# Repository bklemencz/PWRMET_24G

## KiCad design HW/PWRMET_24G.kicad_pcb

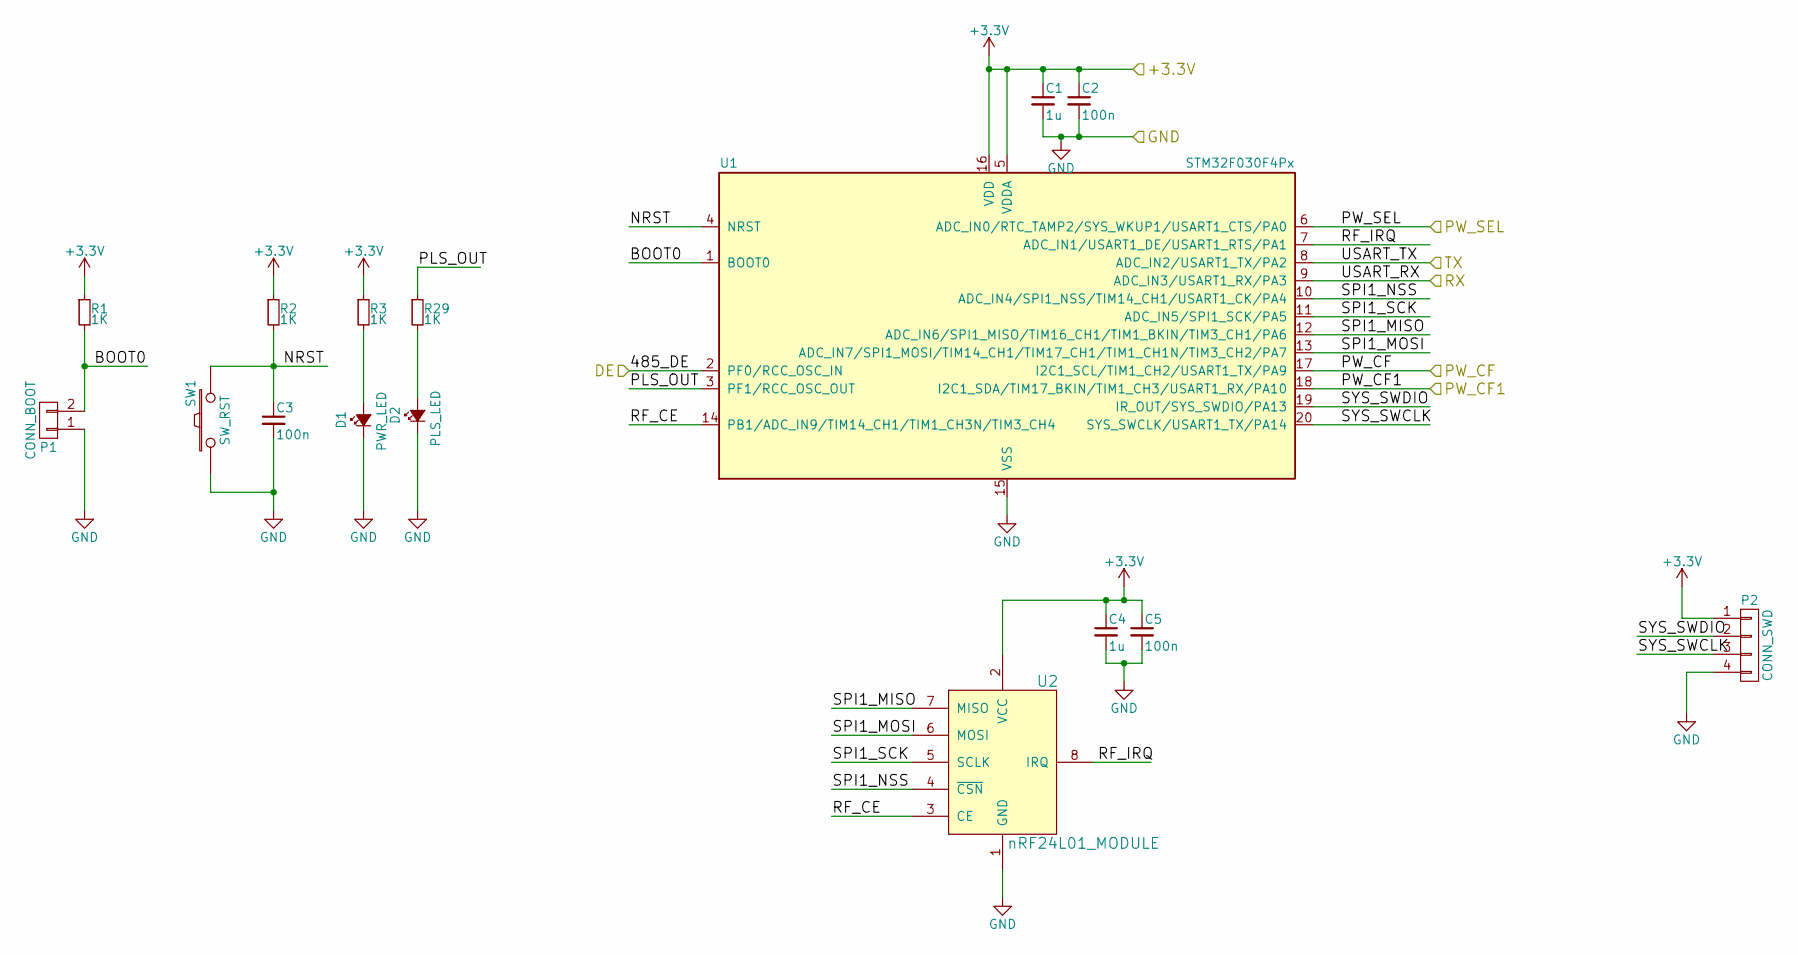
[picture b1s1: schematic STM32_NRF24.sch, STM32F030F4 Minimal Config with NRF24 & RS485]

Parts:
C1, C4: 1u; C_0805
C2, C3, C5: 100n; C_0805
D1: PWR_LED; LED_0805
D2: PLS_LED; LED_D5.0mm
P1: CONN_BOOT; Pin_Header_Straight_1x02_Pitch2.54mm
P2: CONN_SWD; Pin_Header_Straight_1x04_Pitch2.54mm
R1, R2, R3, R29: 1K; R_0805
SW1: SW_RST; SW_SPST_TACT_SMD_3X6
U1: STM32F030F4Px; TSSOP-20_4.4x6.5mm_Pitch0.65mm
U2: nRF24L01_MODULE; NRF24L01_MODULE

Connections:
+3V3: C1.1, C2.1, C4.1, C5.1, P2.1, R1.1, R2.1, R3.1, U1.5 (VDDA), U1.16 (VDD), U2.2 (VCC); also elsewhere on the board
/HLW8012/CF: U1.17 (I2C1_SCL/TIM1_CH2/USART1_TX/PA9); also elsewhere on the board
/HLW8012/CF1: U1.18 (I2C1_SDA/TIM17_BKIN/TIM1_CH3/USART1_RX/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); also elsewhere on the board
/RS485_ISOL/DE: U1.2 (PF0/RCC_OSC_IN); also elsewhere on the board
/RS485_ISOL/RX: U1.9 (ADC_IN3/USART1_RX/PA3); also elsewhere on the board
/RS485_ISOL/TX: U1.8 (ADC_IN2/USART1_TX/PA2); also elsewhere on the board
/STM32_NRF24/BOOT0: P1.2, R1.2, U1.1 (BOOT0)
/STM32_NRF24/NRST: C3.1, R2.2, SW1.2, U1.4 (NRST)
/STM32_NRF24/PLS_OUT: R29.1, U1.3 (PF1/RCC_OSC_OUT)
/STM32_NRF24/PW_SEL: U1.6 (ADC_IN0/RTC_TAMP2/SYS_WKUP1/USART1_CTS/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); also elsewhere on the board
/STM32_NRF24/RF_CE: U1.14 (PB1/ADC_IN9/TIM14_CH1/TIM1_CH3N/TIM3_CH4), U2.3 (CE)
/STM32_NRF24/RF_IRQ: U1.7 (ADC_IN1/USART1_DE/USART1_RTS/PA1), U2.8 (IRQ)
/STM32_NRF24/SPI1_MISO: U1.12 (ADC_IN6/SPI1_MISO/TIM16_CH1/TIM1_BKIN/T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), U2.7 (MISO)
/STM32_NRF24/SPI1_MOSI: U1.13 (ADC_IN7/SPI1_MOSI/TIM14_CH1/TIM17_CH1/T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), U2.6 (MOSI)
/STM32_NRF24/SPI1_NSS: U1.10 (ADC_IN4/SPI1_NSS/TIM14_CH1/USART1_CK/PA4), U2.4 (~CSN)
/STM32_NRF24/SPI1_SCK: U1.11 (ADC_IN5/SPI1_SCK/PA5), U2.5 (SCLK)
/STM32_NRF24/SYS_SWCLK: P2.3, U1.20 (SYS_SWCLK/USART1_TX/PA14)
/STM32_NRF24/SYS_SWDIO: P2.2, U1.19 (IR_OUT/SYS_SWDIO/PA13)
GND: C1.2, C2.2, C3.2, C4.2, C5.2, D1.1 (K), D2.1 (K), P1.1, P2.4, SW1.1, U1.15 (VSS), U2.1 (GND); also elsewhere on the board
unnamed: D1.2 (A), R3.2
unnamed: D2.2 (A), R29.2

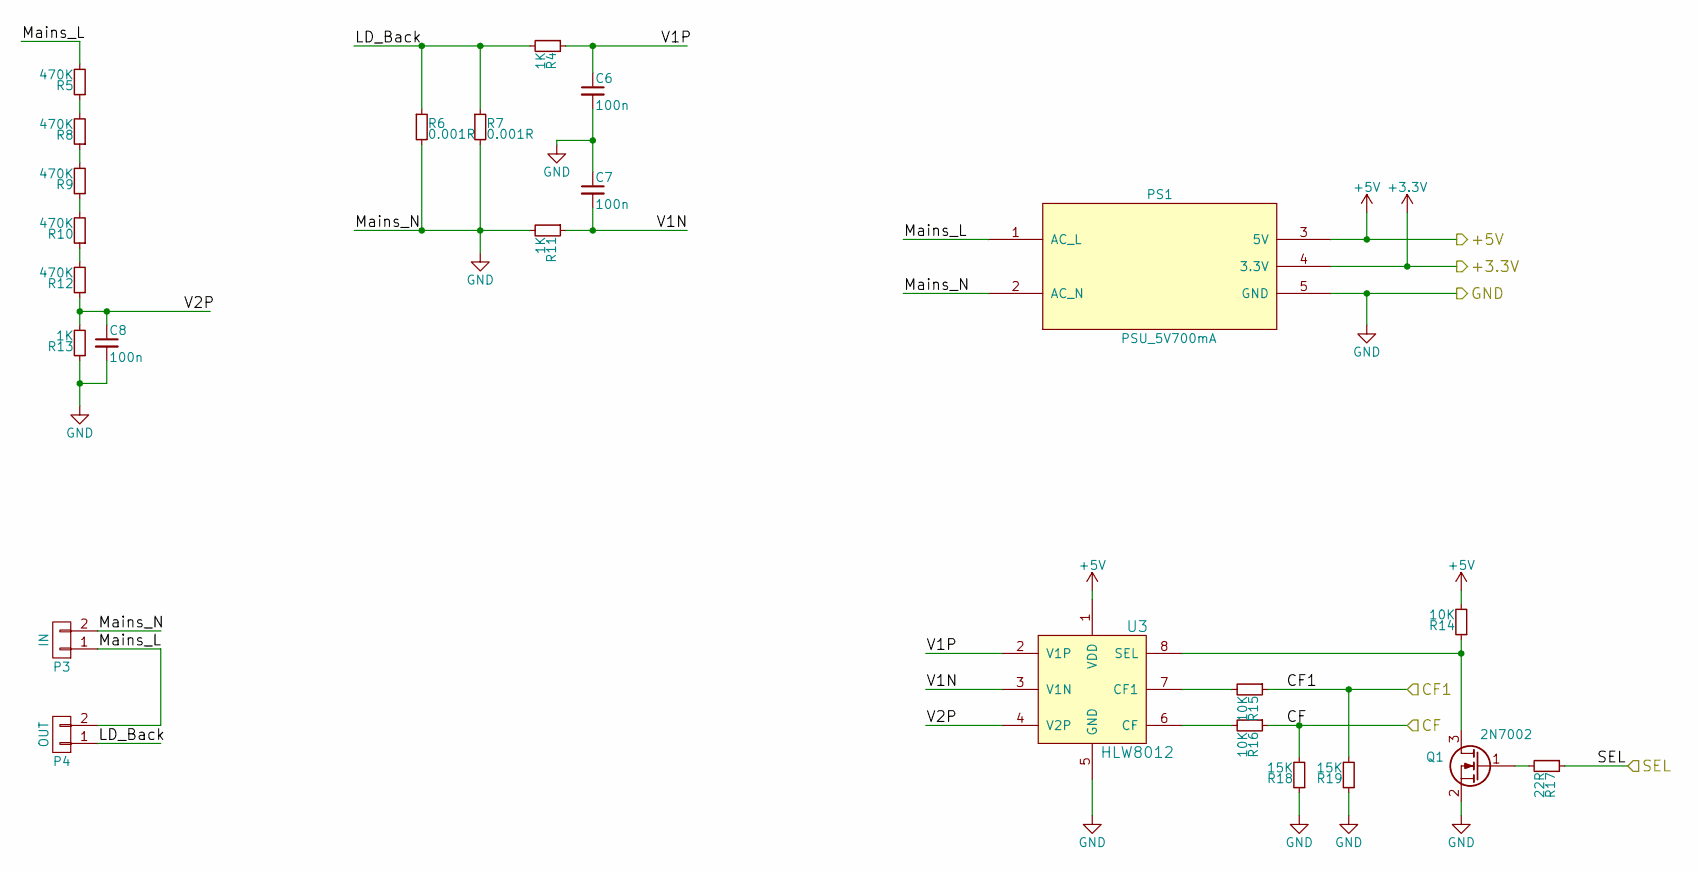
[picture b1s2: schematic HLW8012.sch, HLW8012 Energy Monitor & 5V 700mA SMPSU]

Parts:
C6, C7, C8: 100n; C_1206
P3: IN; TerminalBlock_Pheonix_MKDS1.5-2pol
P4: OUT; TerminalBlock_Pheonix_MKDS1.5-2pol
PS1: PSU_5V700mA; SWPSU_5V_700mA
Q1: 2N7002; SOT-23
R4, R11, R13: 1K; R_1206
R5, R8, R9, R10, R12: 470K; R_1206
R6: 0.001R; R_2512_HandSoldering
R7: 0.001R; Shunt_l10mm_d2mm
R14, R15, R16: 10K; R_0805
R17: 22R; R_0805
R18, R19: 15K; R_0805
U3: HLW8012; SOIC-8_3.9x4.9mm_Pitch1.27mm

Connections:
+3V3: PS1.4 (3.3V); also elsewhere on the board
+5V: PS1.3 (5V), R14.2, U3.1 (VDD)
/HLW8012/CF: R16.1, R18.2; also elsewhere on the board
/HLW8012/CF1: R15.1, R19.2; also elsewhere on the board
/HLW8012/LD_Back: P4.1, R4.2, R6.1, R7.1
/HLW8012/Mains_L: P3.1, P4.2, PS1.1 (AC_L), R5.2
/HLW8012/V1N: C7.2, R11.1, U3.3 (V1N)
/HLW8012/V1P: C6.1, R4.1, U3.2 (V1P)
/HLW8012/V2P: C8.1, R12.1, R13.2, U3.4 (V2P)
/STM32_NRF24/PW_SEL: R17.1; also elsewhere on the board
GND: C6.2, C7.1, C8.2, P3.2, PS1.2 (AC_N), PS1.5 (GND), Q1.2 (S), R6.2, R7.2, R11.2, R13.1, R18.1, R19.1, U3.5 (GND); also elsewhere on the board
unnamed: Q1.1 (G), R17.2
unnamed: Q1.3 (D), R14.1, U3.8 (SEL)
unnamed: R5.1, R8.2
unnamed: R8.1, R9.2
unnamed: R10.1, R12.2
unnamed: R9.1, R10.2
unnamed: R15.2, U3.7 (CF1)
unnamed: R16.2, U3.6 (CF)

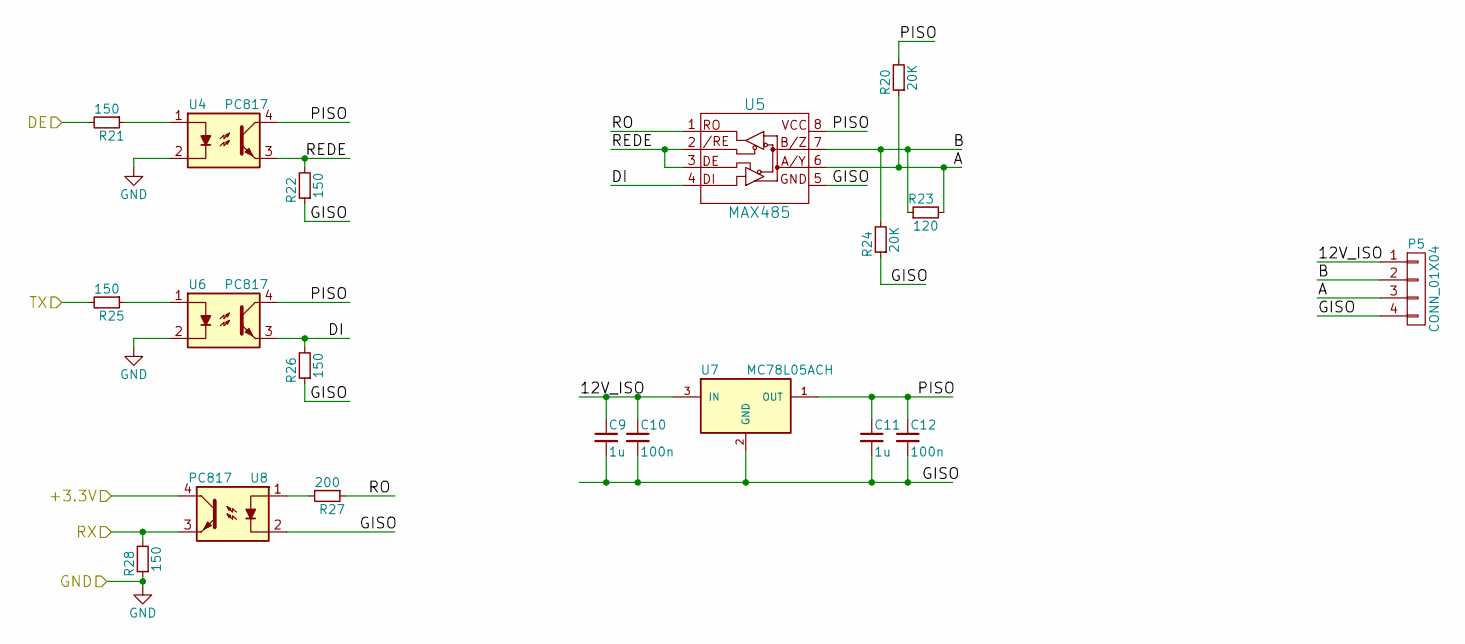
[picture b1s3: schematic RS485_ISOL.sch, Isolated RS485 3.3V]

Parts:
C9, C11: 1u; C_0805
C10, C12: 100n; C_0805
P5: CONN_01X04; Pin_Header_Straight_1x04_Pitch2.54mm
R20, R24: 20K; R_0805
R21, R22, R25, R26, R28: 150; R_0805
R23: 120; R_0805
R27: 200; R_0805
U4, U6, U8: PC817; DIP-4_W9.53mm_SMD
U5: MAX485; SOIC-8_3.9x4.9mm_Pitch1.27mm
U7: MC78L05ACH; SOT-89-3

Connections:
+3V3: U8.4; also elsewhere on the board
/RS485_ISOL/12V_ISO: C9.1, C10.1, P5.1, U7.3 (IN)
/RS485_ISOL/A: P5.3, R20.1, R23.2, U5.6 (A/Y)
/RS485_ISOL/B: P5.2, R23.1, R24.2, U5.7 (B/Z)
/RS485_ISOL/DE: R21.2; also elsewhere on the board
/RS485_ISOL/DI: R26.2, U5.4 (DI), U6.3
/RS485_ISOL/GISO: C9.2, C10.2, C11.2, C12.2, P5.4, R22.1, R24.1, R26.1, U5.5 (GND), U7.2 (GND), U8.2
/RS485_ISOL/PISO: C11.1, C12.1, R20.2, U4.4, U5.8 (VCC), U6.4, U7.1 (OUT)
/RS485_ISOL/REDE: R22.2, U4.3, U5.2 (/RE), U5.3 (DE)
/RS485_ISOL/RO: R27.1, U5.1 (RO)
/RS485_ISOL/RX: R28.2, U8.3; also elsewhere on the board
/RS485_ISOL/TX: R25.2; also elsewhere on the board
GND: R28.1, U4.2, U6.2; also elsewhere on the board
unnamed: R21.1, U4.1
unnamed: R25.1, U6.1
unnamed: R27.2, U8.1

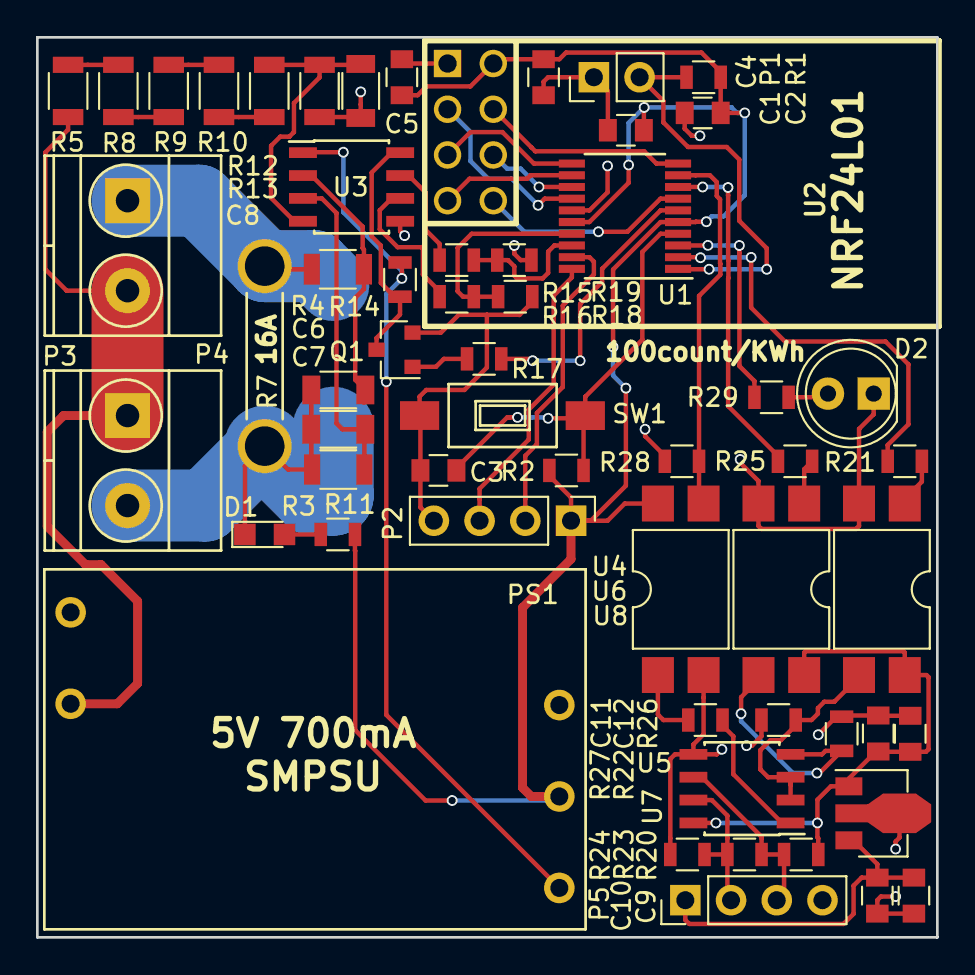
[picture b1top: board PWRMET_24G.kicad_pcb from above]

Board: 2 copper layers, 50.0 x 50.0 mm, 59 parts (1 on the bottom side), 46 nets.

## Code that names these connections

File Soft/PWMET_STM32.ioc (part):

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Mcu.Name=STM32F030F4Px
Mcu.Package=TSSOP20
Mcu.UserName=STM32F030F4Px
PA0.GPIOParameters=GPIO_Label
PA0.GPIO_Label=PW_SEL
PA0.Signal=GPIO_Output
PA1.GPIOParameters=GPIO_Label
PA1.GPIO_Label=RF_IRQ
PA1.Signal=GPIO_Input
PA10.GPIOParameters=GPIO_Label
PA10.GPIO_Label=PW_CF1
PA10.Signal=S_TIM1_CH3
PA13.Mode=Serial_Wire
PA13.Signal=SYS_SWDIO
PA14.Mode=Serial_Wire
PA14.Signal=SYS_SWCLK
PA2.Mode=Asynchronous
PA2.Signal=USART1_TX
PA3.Mode=Asynchronous
PA3.Signal=USART1_RX
PA4.Mode=NSS_Signal_Hard_Output
PA4.Signal=SPI1_NSS
PA5.Mode=Full_Duplex_Master
PA5.Signal=SPI1_SCK
PA6.Mode=Full_Duplex_Master
PA6.Signal=SPI1_MISO
PA7.Mode=Full_Duplex_Master
PA7.Signal=SPI1_MOSI
PA9.GPIOParameters=GPIO_Label
PA9.GPIO_Label=PW_CF
PA9.Signal=S_TIM1_CH2
PB1.GPIOParameters=GPIO_Speed,GPIO_Label
PB1.GPIO_Label=RF_CE
PB1.GPIO_Speed=GPIO_SPEED_FREQ_HIGH
PB1.Signal=GPIO_Output
PF0-OSC_IN.GPIOParameters=GPIO_Speed,GPIO_Label
PF0-OSC_IN.GPIO_Label=DE
PF0-OSC_IN.GPIO_Speed=GPIO_SPEED_FREQ_HIGH
PF0-OSC_IN.Signal=GPIO_Output
PF1-OSC_OUT.GPIOParameters=GPIO_Speed,GPIO_Label
PF1-OSC_OUT.GPIO_Label=RF_POW
PF1-OSC_OUT.GPIO_Speed=GPIO_SPEED_FREQ_HIGH
PF1-OSC_OUT.Signal=GPIO_Output
RCC.SYSCLKFreq_VALUE=48000000
RCC.SYSCLKSource=RCC_SYSCLKSOURCE_PLLCLK

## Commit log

2017-05-18 :octocat: Added .gitattributes & .gitignore files
2017-05-18 Initial
2017-05-22 hw folder
2017-05-24 PCB Start
2017-05-27 PCB Upd
2017-05-28 SCH&PCB Update
2017-05-28 PCB Gerbers
2017-05-30 PCB Update
2017-06-01 PCB_Silk_Update
2017-07-05 Transfer to PIO
2017-07-05 PIO Upd
